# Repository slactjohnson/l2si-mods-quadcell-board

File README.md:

# l2si-mods-quadcell-board
Repository for design files related to the L2SI MODS quad cell PCB.

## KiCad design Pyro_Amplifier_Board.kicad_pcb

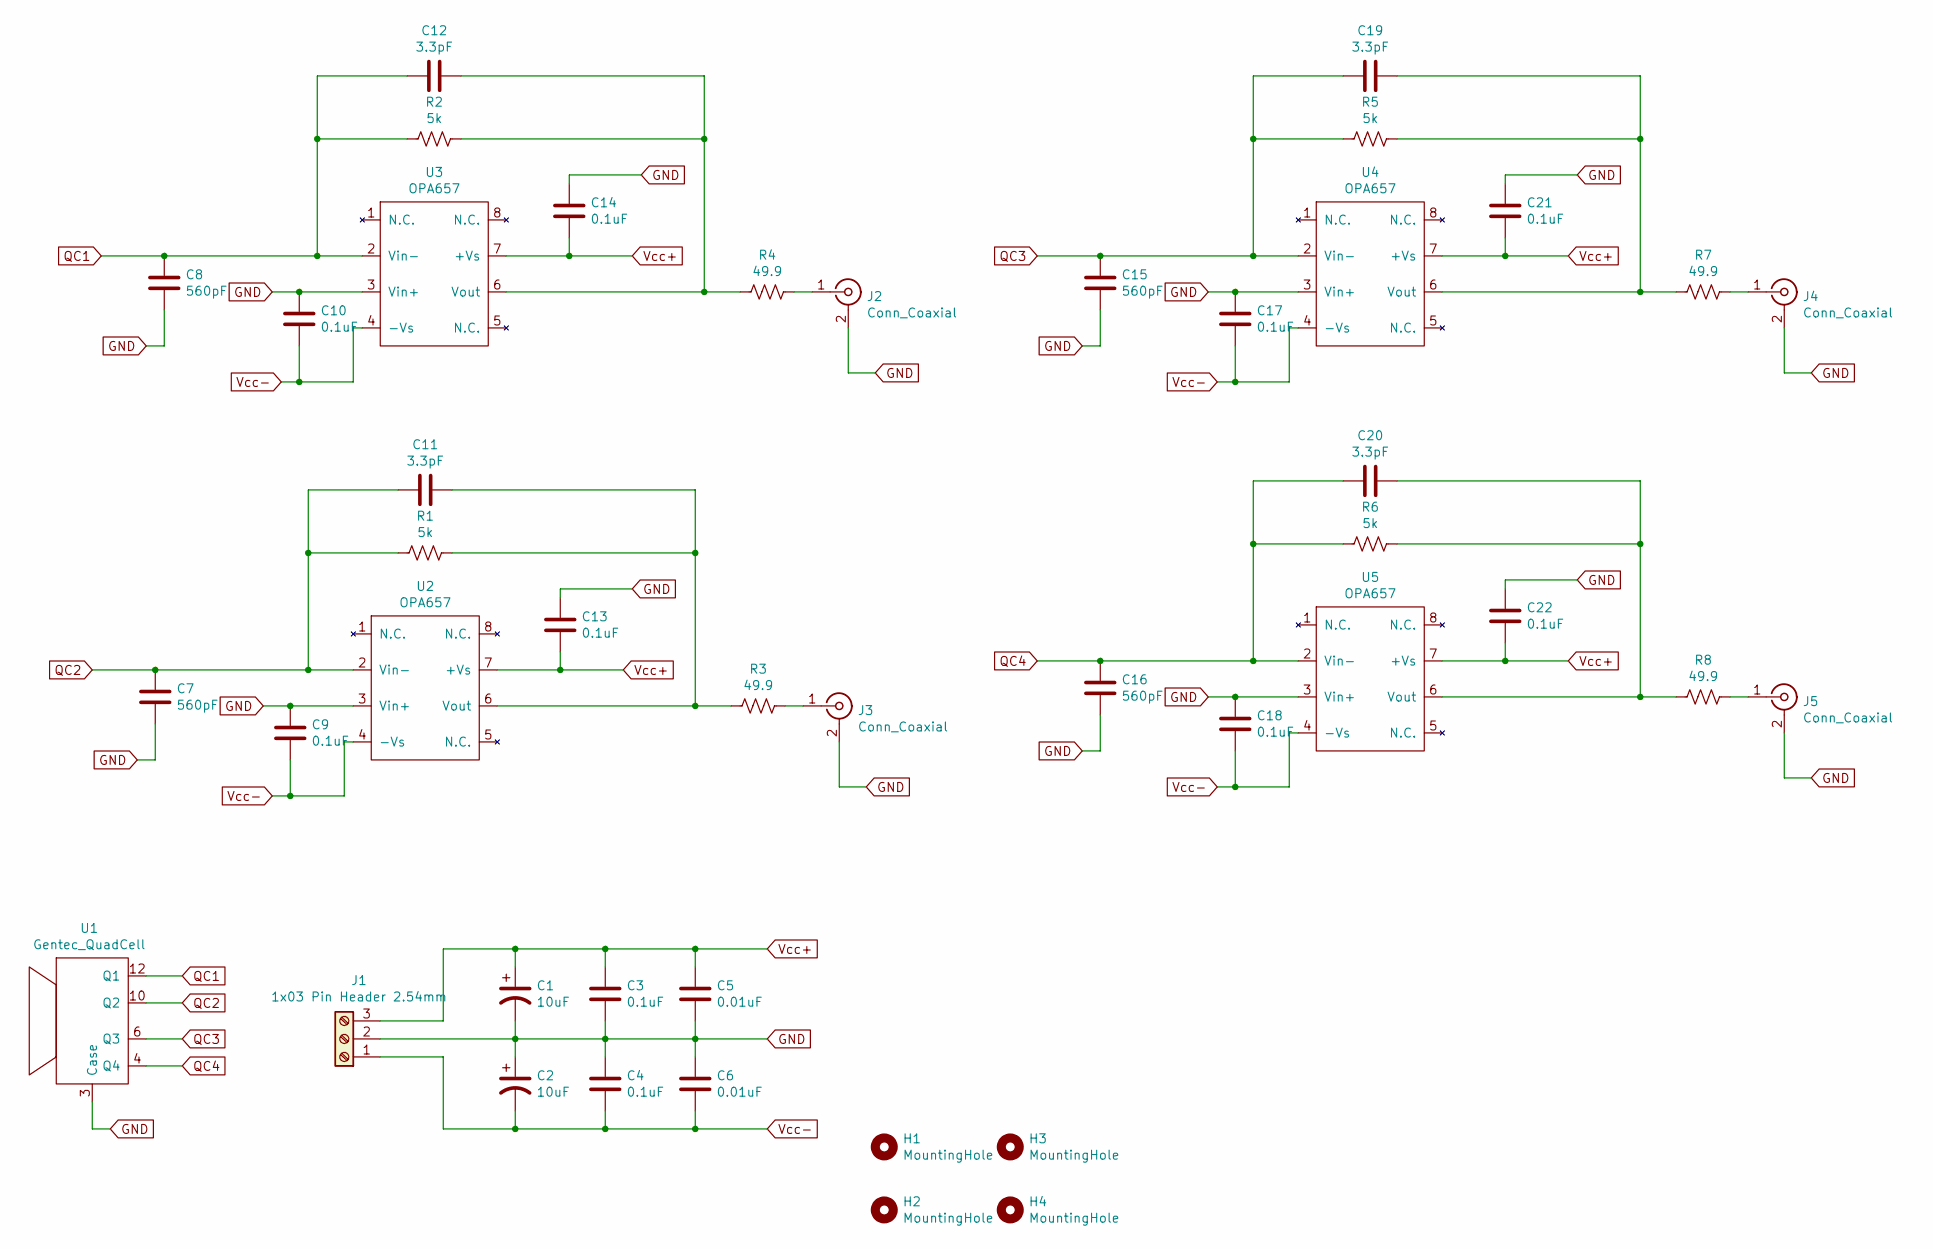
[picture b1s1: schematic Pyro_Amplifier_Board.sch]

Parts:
C1, C2: 10uF; CP_Radial_D10.0mm_P5.00mm
C3, C4, C9, C10, C13, C14, C17, C18, C21, C22: 0.1uF; C_0805_2012Metric_Pad1.15x1.40mm_HandSolder
C5, C6: 0.01uF; C_0805_2012Metric_Pad1.15x1.40mm_HandSolder
C7, C8, C15, C16: 560pF; C_0805_2012Metric_Pad1.15x1.40mm_HandSolder
C11, C12, C19, C20: 3.3pF; C_0805_2012Metric_Pad1.15x1.40mm_HandSolder
H1, H2, H3, H4: MountingHole; ThorLabs_6mm_CageSystem_MountHole
J1: 1x03 Pin Header 2.54mm; PinHeader_1x03_P2.54mm_Horizontal
J2, J3, J4, J5: Conn_Coaxial; SMA_Amphenol_132134-11_Vertical
R1, R2, R5, R6: 5k; R_0805_2012Metric_Pad1.15x1.40mm_HandSolder
R3, R4, R7, R8: 49.9; R_0805_2012Metric_Pad1.15x1.40mm_HandSolder
U1: Gentec_QuadCell; TO-8_Can_12_Leads
U2, U3, U4, U5: OPA657; SOIC-8_3.9x4.9mm_P1.27mm

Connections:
GND: C1.2, C2.1, C3.1, C4.2, C5.1, C6.2, C7.2, C8.2, C9.1, C10.1, C13.2, C14.2, C15.2, C16.2, C17.1, C18.1, C21.2, C22.2, J1.2, J2.2 (Ext), J3.2 (Ext), J4.2 (Ext), J5.2 (Ext), U1.3 (Case), U2.3 (Vin+), U3.3 (Vin+), U4.3 (Vin+), U5.3 (Vin+)
unnamed: C11.1, R1.1, R3.2, U2.6 (Vout)
unnamed: C12.1, R2.1, R4.2, U3.6 (Vout)
unnamed: C19.1, R5.1, R7.2, U4.6 (Vout)
unnamed: C20.1, R6.1, R8.2, U5.6 (Vout)
unnamed: J2.1 (In), R4.1
unnamed: J3.1 (In), R3.1
unnamed: J4.1 (In), R7.1
unnamed: J5.1 (In), R8.1
QC1: C8.1, C12.2, R2.2, U1.12 (Q1), U3.2 (Vin-)
QC2: C7.1, C11.2, R1.2, U1.10 (Q2), U2.2 (Vin-)
QC3: C15.1, C19.2, R5.2, U1.6 (Q3), U4.2 (Vin-)
QC4: C16.1, C20.2, R6.2, U1.4 (Q4), U5.2 (Vin-)
Vcc+: C1.1, C3.2, C5.2, C13.1, C14.1, C21.1, C22.1, J1.3, U2.7 (+Vs), U3.7 (+Vs), U4.7 (+Vs), U5.7 (+Vs)
Vcc-: C2.2, C4.1, C6.1, C9.2, C10.2, C17.2, C18.2, J1.1, U2.4 (-Vs), U3.4 (-Vs), U4.4 (-Vs), U5.4 (-Vs)

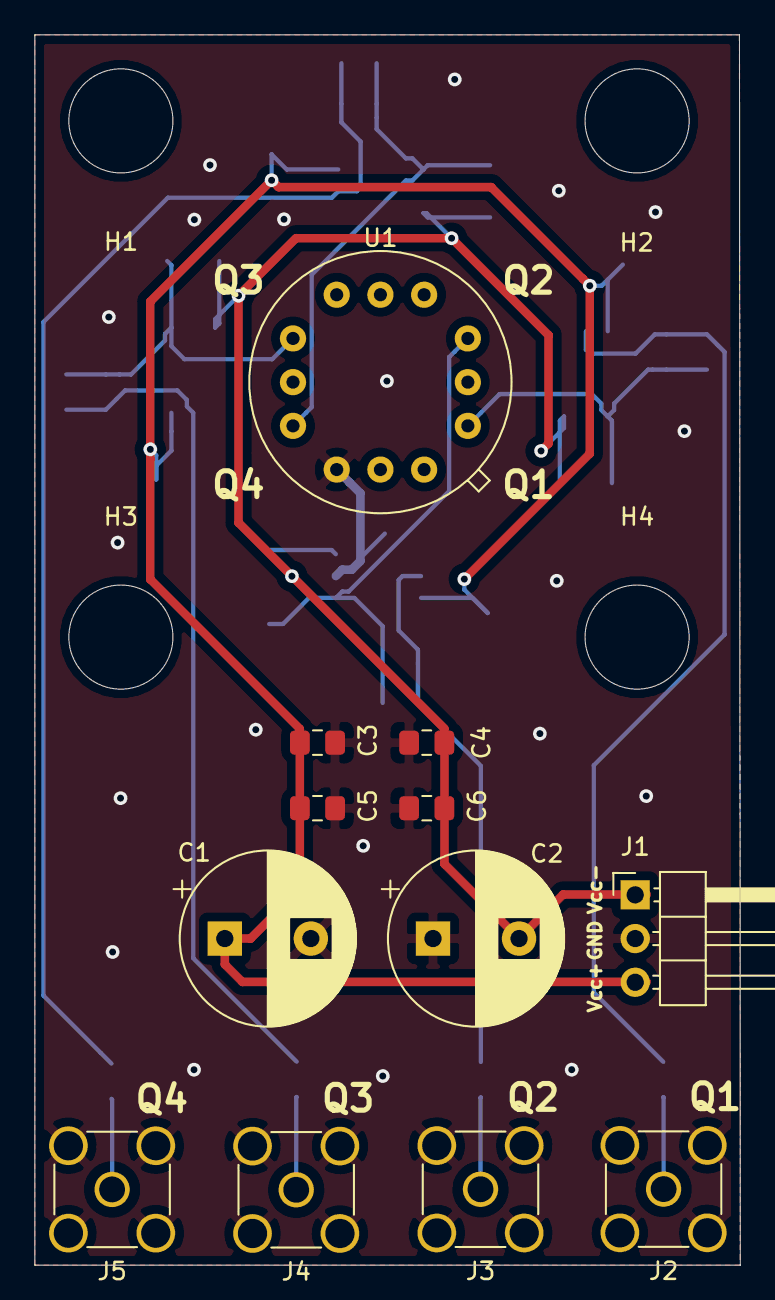
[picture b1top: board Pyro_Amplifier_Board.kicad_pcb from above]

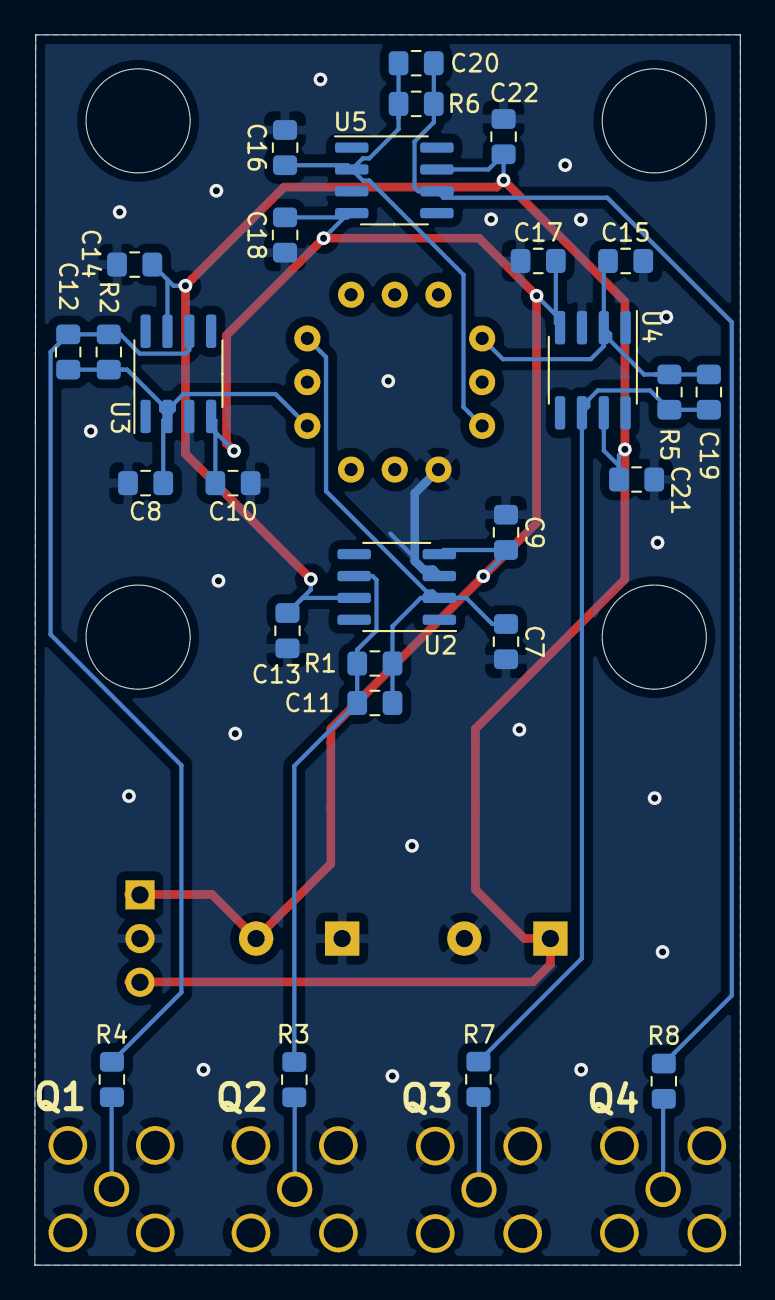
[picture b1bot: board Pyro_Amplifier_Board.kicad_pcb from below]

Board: 2 copper layers, 41.0 x 71.5 mm, 44 parts (28 on the bottom side), 15 nets.

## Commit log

2020-09-14 Initial commit of design files.
